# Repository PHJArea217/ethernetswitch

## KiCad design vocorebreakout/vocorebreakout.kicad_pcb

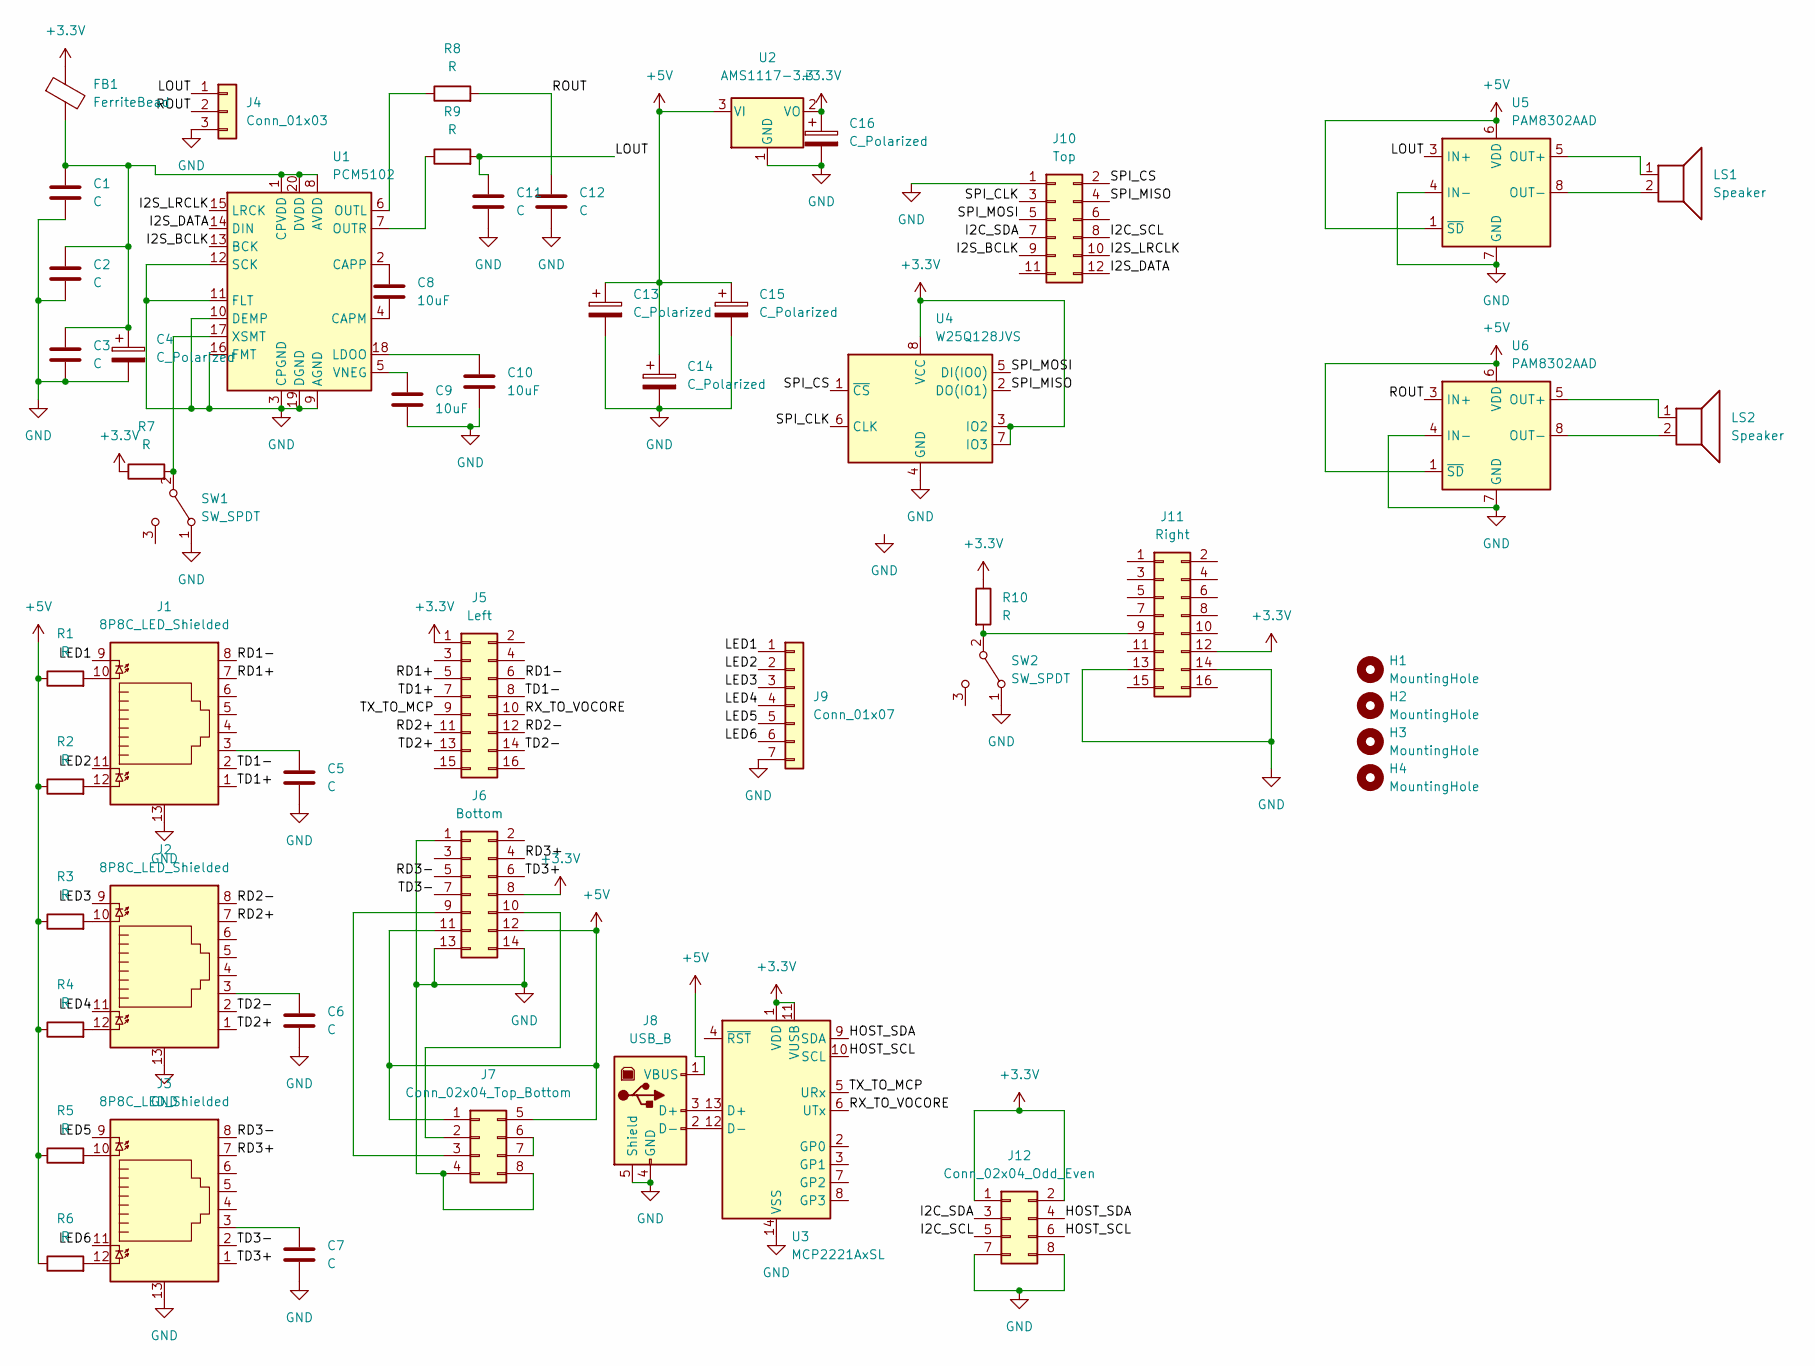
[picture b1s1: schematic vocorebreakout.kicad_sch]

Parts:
C1, C2, C3, C5, C6, C7, C11, C12: C; C_0603_1608Metric
C4, C13, C14, C15, C16: C_Polarized; CP_Radial_D8.0mm_P3.50mm
C8, C9, C10: 10uF; C_0805_2012Metric
FB1: FerriteBead; R_1206_3216Metric
H1, H2, H3, H4: MountingHole; MountingHole_3.2mm_M3
J1, J2, J3: 8P8C_LED_Shielded; RJ45_Cetus_J1B1211CCD_Horizontal
J4: Conn_01x03; PinHeader_1x03_P2.54mm_Vertical
J5: Left; PinHeader_2x08_P2.54mm_Vertical
J6: Bottom; PinHeader_2x07_P2.54mm_Vertical
J7: Conn_02x04_Top_Bottom; USB_A_Wuerth_61400826021_Horizontal_Stacked
J8: USB_B; USB_B_OST_USB-B1HSxx_Horizontal
J9: Conn_01x07; PinHeader_1x07_P2.54mm_Vertical
J10: Top; PinHeader_2x06_P2.54mm_Vertical
J11: Right; PinHeader_2x08_P2.54mm_Vertical
J12: Conn_02x04_Odd_Even; PinHeader_2x04_P2.54mm_Vertical
LS1, LS2: Speaker; PinHeader_1x02_P2.54mm_Vertical
R1, R2, R3, R4, R5, R6, R7, R8, R9, R10: R; R_0603_1608Metric
SW1, SW2: SW_SPDT; PinHeader_1x03_P2.54mm_Vertical
U1: PCM5102; TSSOP-20_4.4x6.5mm_P0.65mm
U2: AMS1117-3.3; SOT-223-3_TabPin2
U3: MCP2221AxSL; SOIC-14_3.9x8.7mm_P1.27mm
U4: W25Q128JVS; SOIC-8_5.23x5.23mm_P1.27mm
U5, U6: PAM8302AAD; SOIC-8_3.9x4.9mm_P1.27mm

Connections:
+3.3V: C16.1, FB1.1, J5.1, J6.8, J11.12, J12.1, J12.2, R7.1, R10.1, U2.2 (VO), U3.1 (VDD), U3.11 (VUSB), U4.3 (IO2), U4.7 (IO3), U4.8 (VCC)
+5V: C13.1, C14.1, C15.1, J6.11, J6.12, J7.1, J7.5, J8.1 (VBUS), R1.1, R2.1, R3.1, R4.1, R5.1, R6.1, U2.3 (VI), U5.1 (~SD), U5.6 (VDD), U6.1 (~SD), U6.6 (VDD)
/HOST_SCL: J12.6, U3.10 (SCL)
/HOST_SDA: J12.4, U3.9 (SDA)
/I2C_SCL: J10.8, J12.5
/I2C_SDA: J10.7, J12.3
/I2S_BCLK: J10.9, U1.13 (BCK)
/I2S_DATA: J10.12, U1.14 (DIN)
/I2S_LRCLK: J10.10, U1.15 (LRCK)
/LED1: J1.9, J9.1
/LED2: J1.11, J9.2
/LED3: J2.9, J9.3
/LED4: J2.11, J9.4
/LED5: J3.9, J9.5
/LED6: J3.11, J9.6
/LOUT: C11.1, J4.1, R9.2, U5.3 (IN+)
/RD1+: J1.7, J5.5
/RD1-: J1.8, J5.6
/RD2+: J2.7, J5.11
/RD2-: J2.8, J5.12
/RD3+: J3.7, J6.4
/RD3-: J3.8, J6.5
/ROUT: C12.1, J4.2, R8.2, U6.3 (IN+)
/RX_TO_VOCORE: J5.10, U3.6 (UTx)
/SPI_CLK: J10.3, U4.6 (CLK)
/SPI_CS: J10.2, U4.1 (~CS)
/SPI_MISO: J10.4, U4.2 (DO(IO1))
/SPI_MOSI: J10.5, U4.5 (DI(IO0))
/TD1+: J1.1, J5.7
/TD1-: J1.2, J5.8
/TD2+: J2.1, J5.13
/TD2-: J2.2, J5.14
/TD3+: J3.1, J6.6
/TD3-: J3.2, J6.7
/TX_TO_MCP: J5.9, U3.5 (URx)
GND: C1.2, C2.2, C3.2, C4.2, C5.2, C6.2, C7.2, C9.2, C10.2, C11.2, C12.2, C13.2, C14.2, C15.2, C16.2, J1.13, J2.13, J3.13, J4.3, J6.1, J6.13, J6.14, J7.4, J7.8, J8.4 (GND), J8.5 (Shield), J9.7, J10.1, J11.13, J11.14, J12.7, J12.8, SW1.1 (A), SW2.1 (A), U1.3 (CPGND), U1.9 (AGND), U1.10 (DEMP), U1.11 (FLT), U1.12 (SCK), U1.16 (FMT), U1.19 (DGND), U2.1 (GND), U3.14 (VSS), U4.4 (GND), U5.4 (IN-), U5.7 (GND), U6.4 (IN-), U6.7 (GND)
unnamed: C1.1, C2.1, C3.1, C4.1, FB1.2, U1.1 (CPVDD), U1.8 (AVDD), U1.20 (DVDD)
unnamed: C5.1, J1.3
unnamed: C6.1, J2.3
unnamed: C7.1, J3.3
unnamed: C8.1, U1.2 (CAPP)
unnamed: C8.2, U1.4 (CAPM)
unnamed: C9.1, U1.5 (VNEG)
unnamed: C10.1, U1.18 (LDOO)
unnamed: J1.10, R1.2
unnamed: J1.12, R2.2
unnamed: J2.10, R3.2
unnamed: J2.12, R4.2
unnamed: J3.10, R5.2
unnamed: J3.12, R6.2
unnamed: J6.9, J7.3
unnamed: J6.10, J7.2
unnamed: J7.6, J7.7
unnamed: J8.2 (D-), U3.12 (D-)
unnamed: J8.3 (D+), U3.13 (D+)
unnamed: J11.9, R10.2, SW2.2 (B)
unnamed: LS1.1, U5.5 (OUT+)
unnamed: LS1.2, U5.8 (OUT-)
unnamed: LS2.1, U6.5 (OUT+)
unnamed: LS2.2, U6.8 (OUT-)
unnamed: R7.2, SW1.2 (B), U1.17 (XSMT)
unnamed: R8.1, U1.6 (OUTL)
unnamed: R9.1, U1.7 (OUTR)

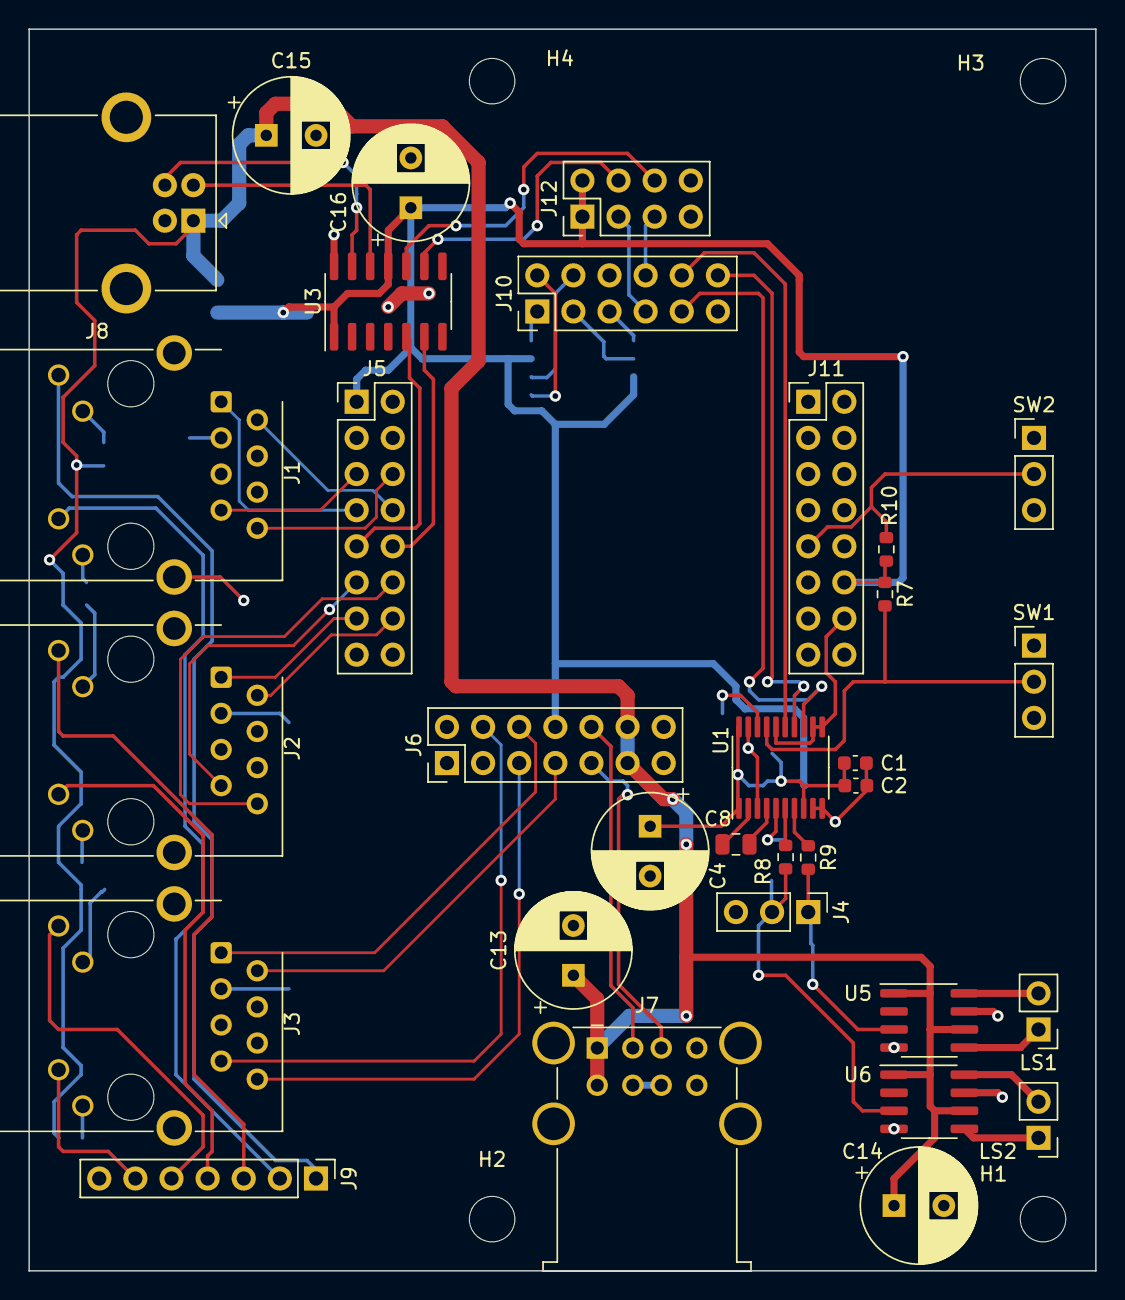
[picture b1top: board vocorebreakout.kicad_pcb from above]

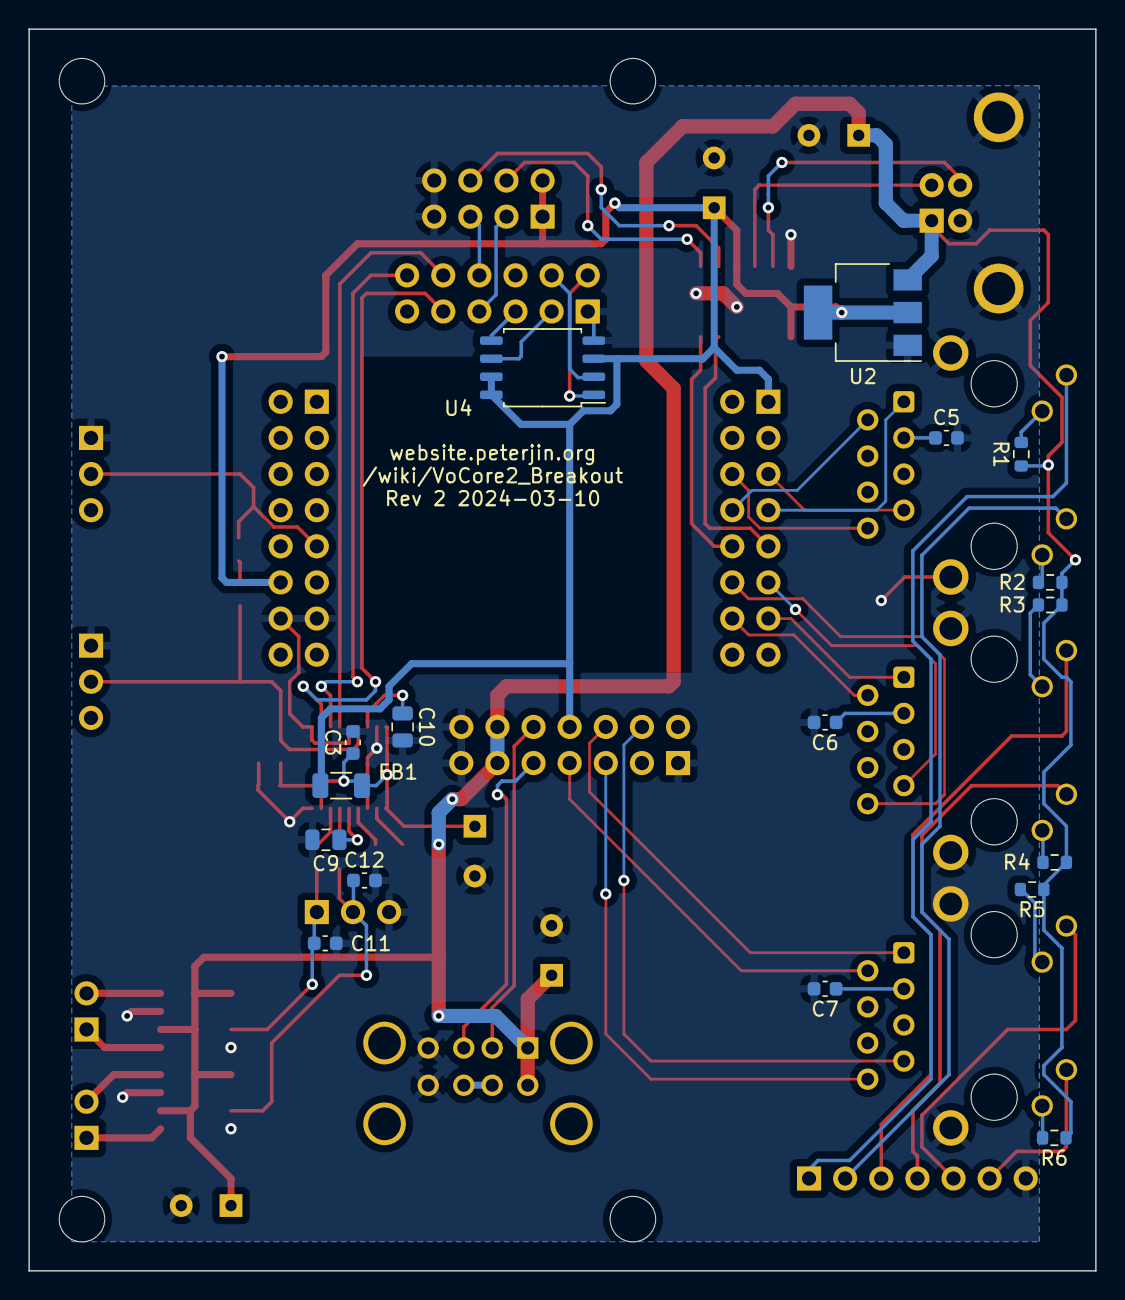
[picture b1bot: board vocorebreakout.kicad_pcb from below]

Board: 2 copper layers, 75.0 x 87.3 mm, 53 parts (17 on the bottom side), 63 nets.

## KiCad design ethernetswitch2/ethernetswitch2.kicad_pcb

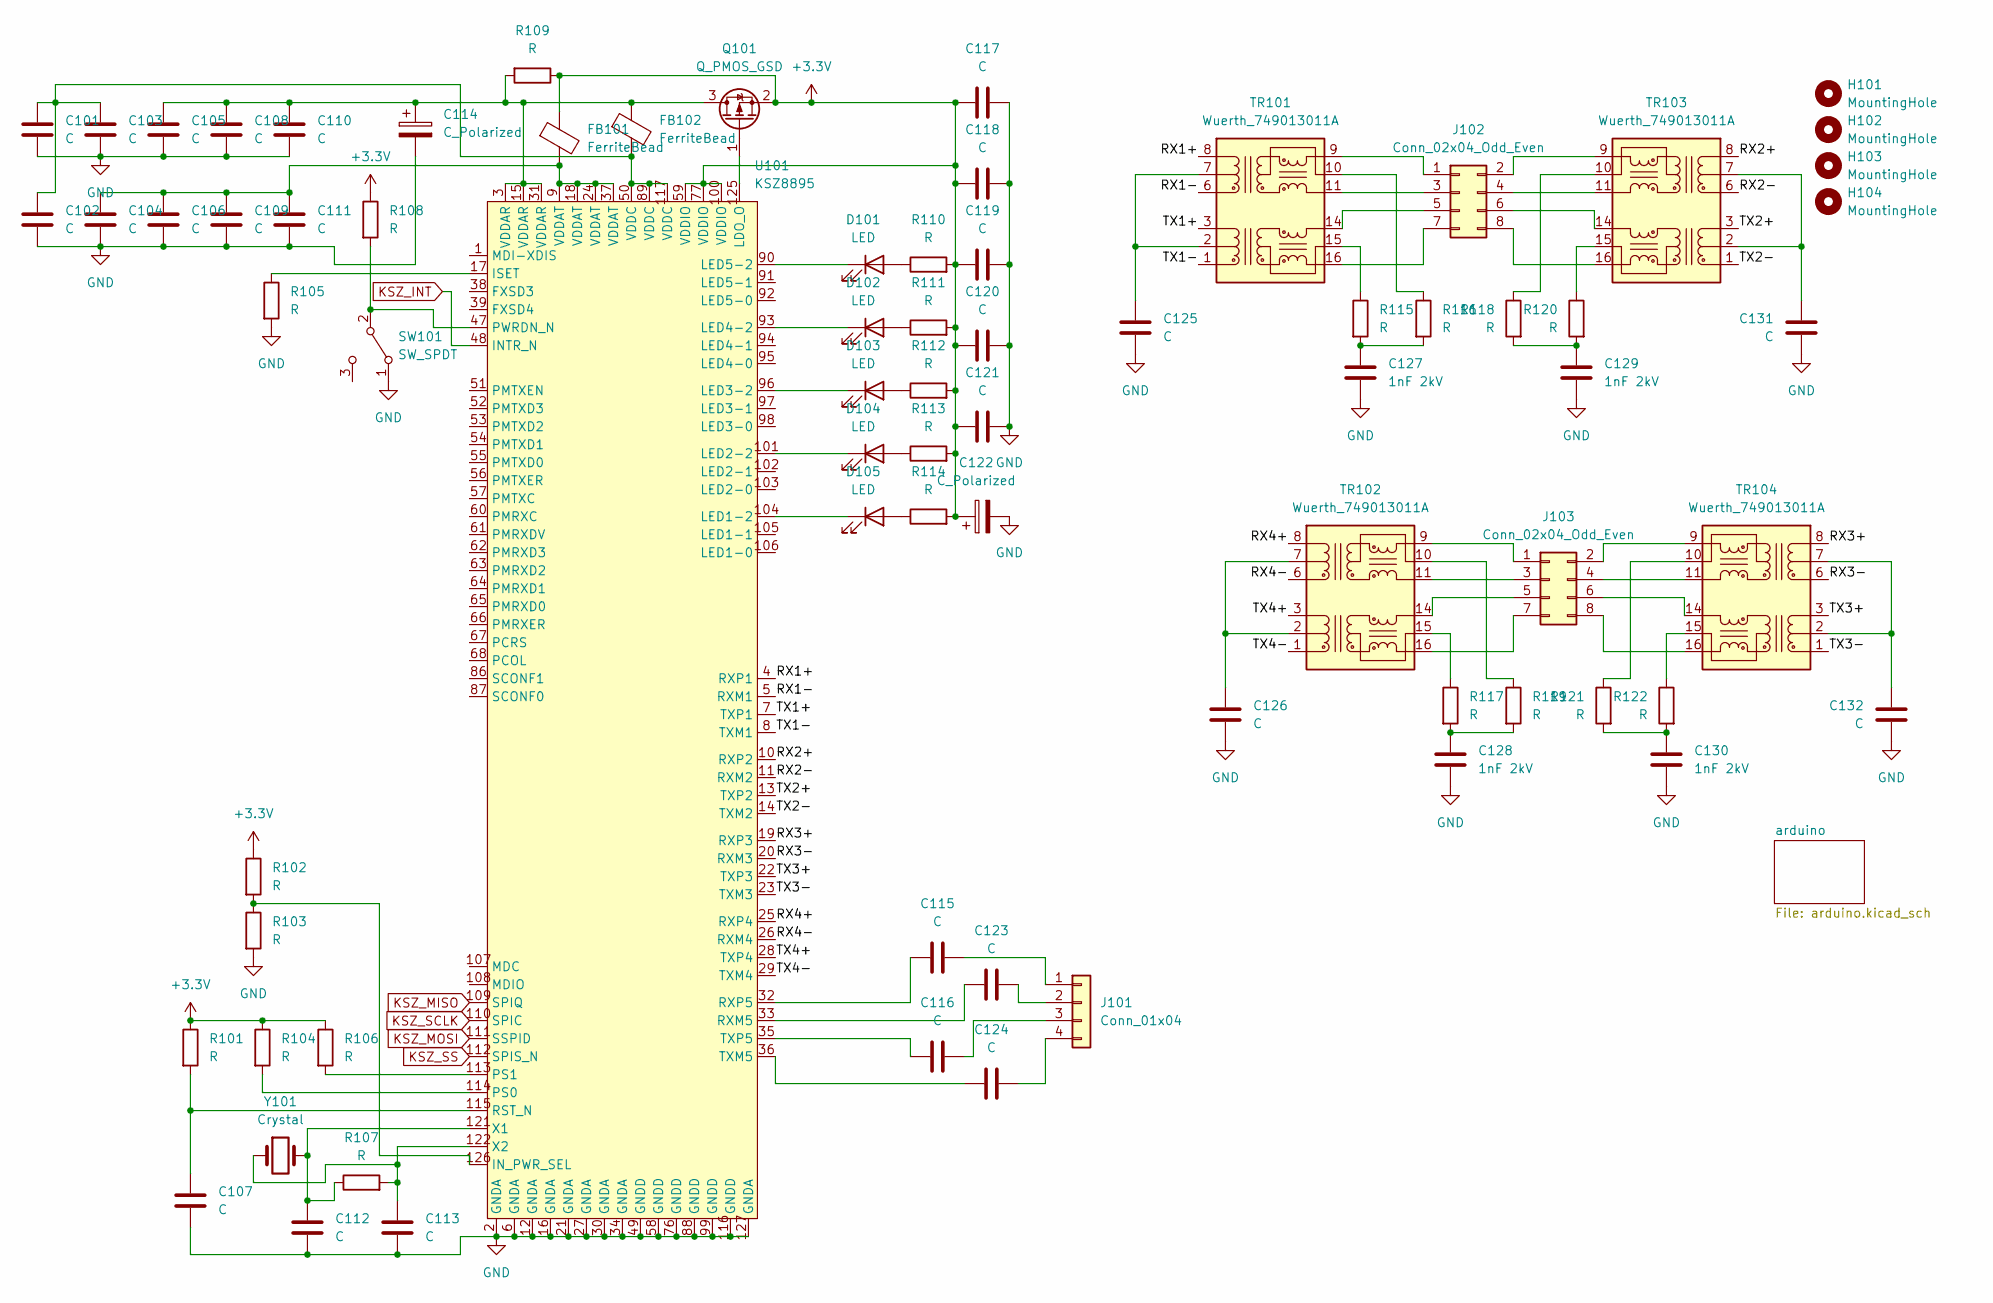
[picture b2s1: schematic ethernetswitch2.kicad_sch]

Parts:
C101, C102, C103, C104, C105, C106, C107, C108, C109, C110, C111, C112, C113, C115, C116, C117, C118, C119, C120, C121, C123, C124, C125, C126, C131, C132: C; C_0603_1608Metric
C114, C122: C_Polarized; CP_Radial_D8.0mm_P3.50mm
C127, C128, C129, C130: 1nF 2kV; C_1206_3216Metric
D101, D102, D103, D104, D105: LED; C_0603_1608Metric
FB101, FB102: FerriteBead; C_1206_3216Metric
H101, H102, H103, H104: MountingHole; MountingHole_3.2mm_M3
J101: Conn_01x04; PinHeader_1x04_P2.54mm_Vertical
J102, J103: Conn_02x04_Odd_Even; PinHeader_2x04_P2.54mm_Vertical
Q101: Q_PMOS_GSD; SOT-23-3
R101, R102, R103, R104, R105, R106, R107, R108, R109, R110, R111, R112, R113, R114, R115, R116, R117, R118, R119, R120, R121, R122: R; R_0603_1608Metric
SW101: SW_SPDT; PinHeader_1x03_P2.54mm_Vertical
TR101, TR102, TR103, TR104: Wuerth_749013011A; Transformer_Ethernet_Wuerth_749013011A
U101: KSZ8895; LQFP-128_14x20mm_P0.5mm
Y101: Crystal; Crystal_HC49-U_Vertical

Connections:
+3.3V: C117.1, C118.1, C119.1, C120.1, C121.1, C122.1, FB101.1, Q101.2 (S), R101.1, R102.1, R104.1, R106.1, R108.1, R109.1, R110.2, R111.2, R112.2, R113.2, R114.2, U101.59 (VDDIO), U101.77 (VDDIO), U101.100 (VDDIO); also elsewhere on the board
/RX1+: TR101.8 (RD-), U101.4 (RXP1)
/RX1-: TR101.6 (RD+), U101.5 (RXM1)
/RX2+: TR103.8 (RD-), U101.10 (RXP2)
/RX2-: TR103.6 (RD+), U101.11 (RXM2)
/RX3+: TR104.8 (RD-), U101.19 (RXP3)
/RX3-: TR104.6 (RD+), U101.20 (RXM3)
/RX4+: TR102.8 (RD-), U101.25 (RXP4)
/RX4-: TR102.6 (RD+), U101.26 (RXM4)
/TX1+: TR101.3 (TD-), U101.7 (TXP1)
/TX1-: TR101.1 (TD+), U101.8 (TXM1)
/TX2+: TR103.3 (TD-), U101.13 (TXP2)
/TX2-: TR103.1 (TD+), U101.14 (TXM2)
/TX3+: TR104.3 (TD-), U101.22 (TXP3)
/TX3-: TR104.1 (TD+), U101.23 (TXM3)
/TX4+: TR102.3 (TD-), U101.28 (TXP4)
/TX4-: TR102.1 (TD+), U101.29 (TXM4)
GND: C101.2, C102.2, C103.2, C104.2, C105.2, C106.2, C107.2, C108.2, C109.2, C110.2, C111.2, C112.2, C113.2, C114.2, C117.2, C118.2, C119.2, C120.2, C121.2, C122.2, C125.2, C126.2, C127.2, C128.2, C129.2, C130.2, C131.2, C132.2, R103.2, R105.2, SW101.1 (A), U101.2 (GNDA), U101.6 (GNDA), U101.12 (GNDA), U101.16 (GNDA), U101.21 (GNDA), U101.27 (GNDA), U101.30 (GNDA), U101.34 (GNDA), U101.49 (GNDD), U101.58 (GNDD), U101.76 (GNDD), U101.88 (GNDD), U101.99 (GNDD), U101.116 (GNDD), U101.127 (GNDA); also elsewhere on the board
KSZ_INT: U101.48 (INTR_N); also elsewhere on the board
KSZ_MISO: U101.109 (SPIQ); also elsewhere on the board
KSZ_MOSI: U101.111 (SSPID); also elsewhere on the board
KSZ_SCLK: U101.110 (SPIC); also elsewhere on the board
KSZ_SS: U101.112 (SPIS_N); also elsewhere on the board
unnamed: C101.1, C102.1, C103.1, FB102.2, U101.50 (VDDC), U101.89 (VDDC), U101.117 (VDDC)
unnamed: C104.1, C106.1, C109.1, C111.1, FB101.2, U101.9 (VDDAT), U101.18 (VDDAT), U101.24 (VDDAT), U101.37 (VDDAT)
unnamed: C105.1, C108.1, C110.1, C114.1, FB102.1, Q101.3 (D), R109.2, U101.3 (VDDAR), U101.15 (VDDAR), U101.31 (VDDAR)
unnamed: C107.1, R101.2, U101.115 (RST_N)
unnamed: C112.1, R107.1, U101.121 (X1), Y101.2
unnamed: C113.1, R107.2, U101.122 (X2), Y101.1
unnamed: C115.1, U101.32 (RXP5)
unnamed: C115.2, J101.1
unnamed: C116.1, U101.35 (TXP5)
unnamed: C116.2, J101.3
unnamed: C123.1, U101.33 (RXM5)
unnamed: C123.2, J101.2
unnamed: C124.1, U101.36 (TXM5)
unnamed: C124.2, J101.4
unnamed: C125.1, TR101.2 (C_TD), TR101.7 (C_RD)
unnamed: C126.1, TR102.2 (C_TD), TR102.7 (C_RD)
unnamed: C127.1, R115.2, R116.2
unnamed: C128.1, R117.2, R119.2
unnamed: C129.1, R118.2, R120.2
unnamed: C130.1, R121.2, R122.2
unnamed: C131.1, TR103.2 (C_TD), TR103.7 (C_RD)
unnamed: C132.1, TR104.2 (C_TD), TR104.7 (C_RD)
unnamed: D101.1 (K), U101.90 (LED5-2)
unnamed: D101.2 (A), R110.1
unnamed: D102.1 (K), U101.93 (LED4-2)
unnamed: D102.2 (A), R111.1
unnamed: D103.1 (K), U101.96 (LED3-2)
unnamed: D103.2 (A), R112.1
unnamed: D104.1 (K), U101.101 (LED2-2)
unnamed: D104.2 (A), R113.1
unnamed: D105.1 (K), U101.104 (LED1-2)
unnamed: D105.2 (A), R114.1
unnamed: J102.1, TR101.9 (RX-)
unnamed: J102.2, TR103.9 (RX-)
unnamed: J102.3, TR101.11 (RX+)
unnamed: J102.4, TR103.11 (RX+)
unnamed: J102.5, TR101.14 (TX-)
unnamed: J102.6, TR103.14 (TX-)
unnamed: J102.7, TR101.16 (TX+)
unnamed: J102.8, TR103.16 (TX+)
unnamed: J103.1, TR102.9 (RX-)
unnamed: J103.2, TR104.9 (RX-)
unnamed: J103.3, TR102.11 (RX+)
unnamed: J103.4, TR104.11 (RX+)
unnamed: J103.5, TR102.14 (TX-)
unnamed: J103.6, TR104.14 (TX-)
unnamed: J103.7, TR102.16 (TX+)
unnamed: J103.8, TR104.16 (TX+)
unnamed: Q101.1 (G), U101.125 (LDO_O)
unnamed: R102.2, R103.1, U101.126 (IN_PWR_SEL)
unnamed: R104.2, U101.114 (PS0)
unnamed: R105.1, U101.17 (ISET)
unnamed: R106.2, U101.113 (PS1)
unnamed: R108.2, SW101.2 (B), U101.47 (PWRDN_N)
unnamed: R115.1, TR101.15 (C_TX)
unnamed: R116.1, TR101.10 (C_RX)
unnamed: R117.1, TR102.15 (C_TX)
unnamed: R118.1, TR103.10 (C_RX)
unnamed: R119.1, TR102.10 (C_RX)
unnamed: R120.1, TR103.15 (C_TX)
unnamed: R121.1, TR104.10 (C_RX)
unnamed: R122.1, TR104.15 (C_TX)

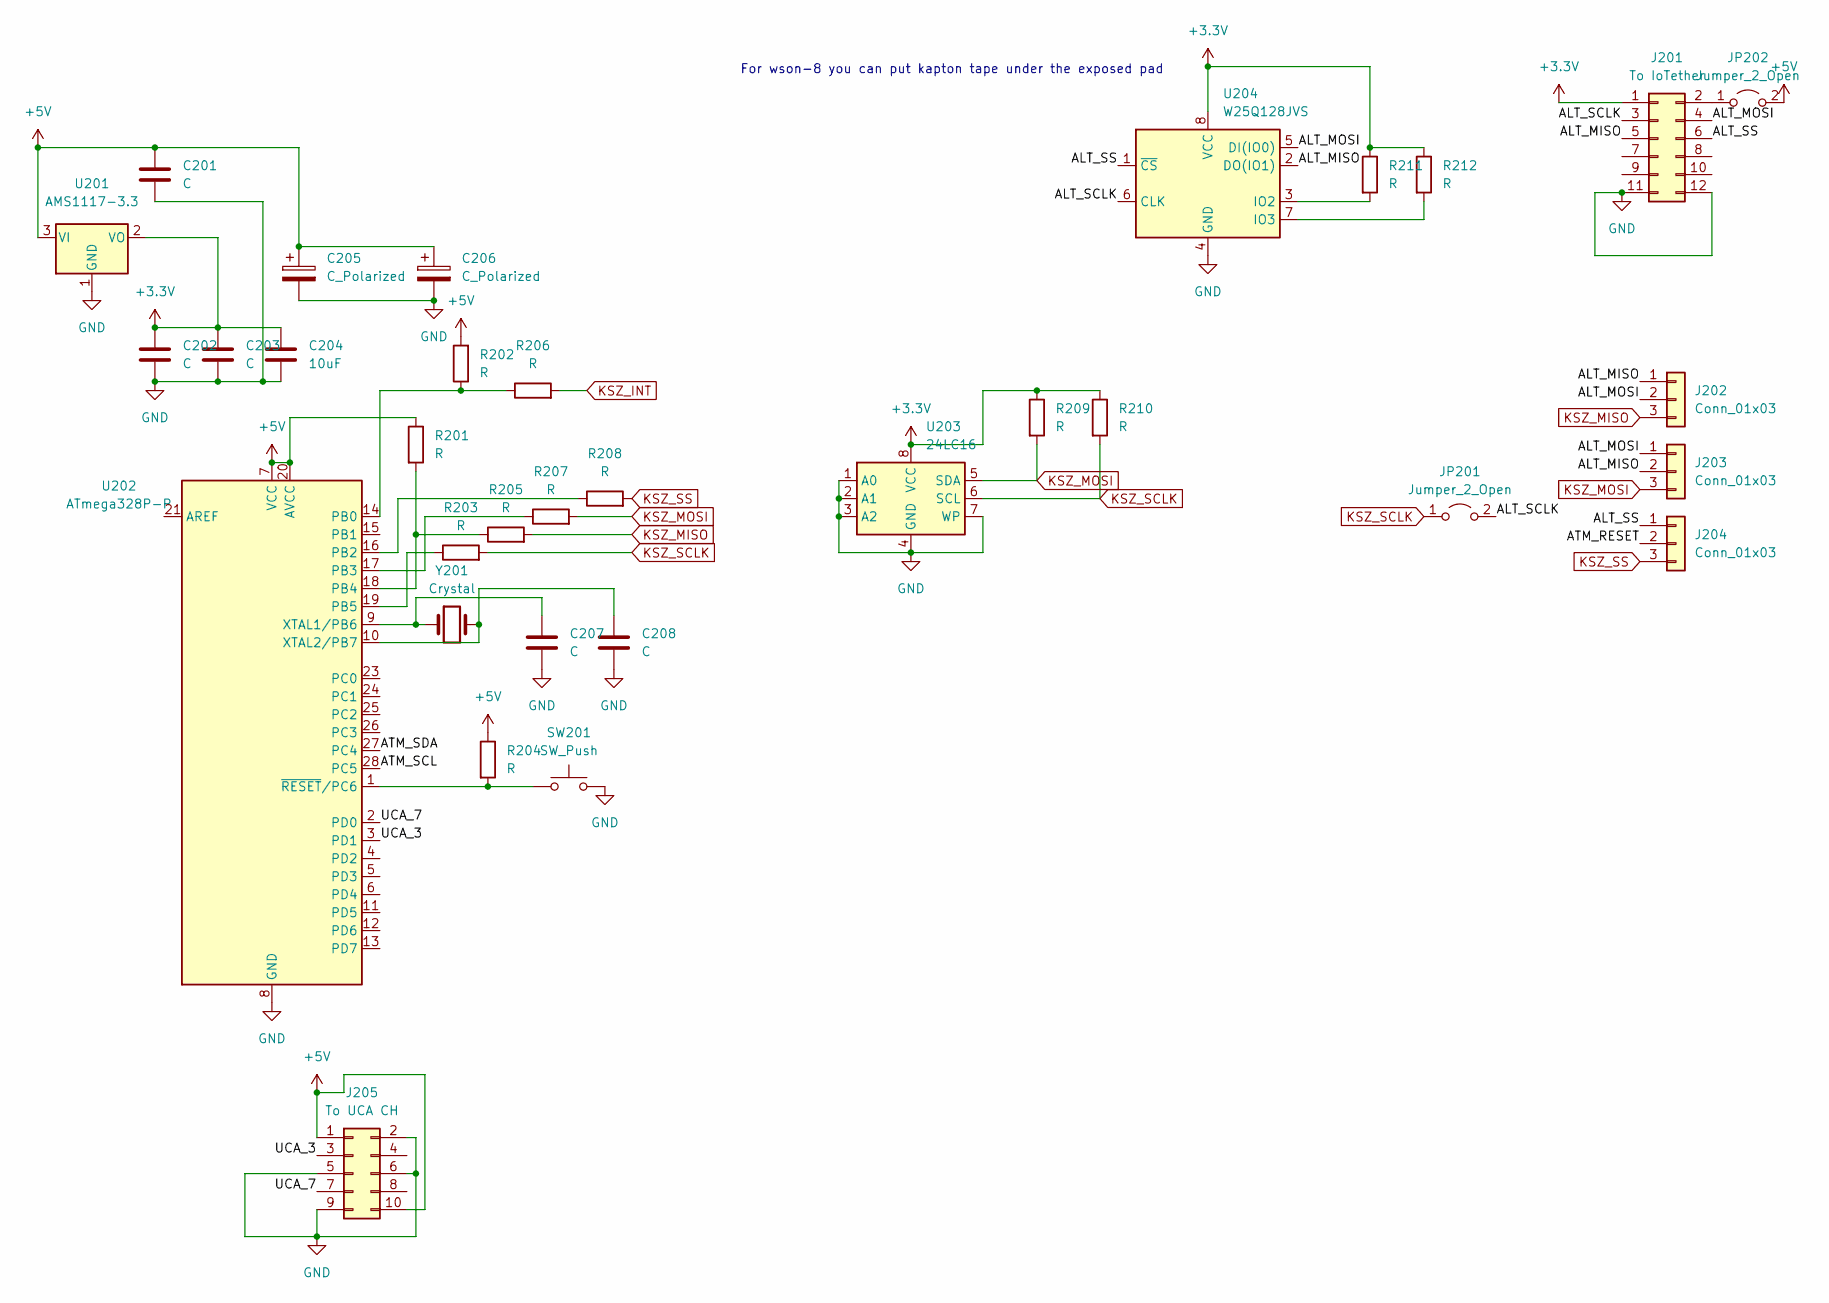
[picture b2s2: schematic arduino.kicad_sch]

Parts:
C201, C202, C203, C207, C208: C; C_0603_1608Metric
C204: 10uF; C_0805_2012Metric
C205, C206: C_Polarized; CP_Radial_D8.0mm_P3.50mm
J201: To IoTether; PinHeader_2x06_P2.54mm_Vertical
J202, J203, J204: Conn_01x03; SOT-23-3
J205: To UCA CH; PinHeader_2x05_P2.54mm_Horizontal
JP201, JP202: Jumper_2_Open; R_0603_1608Metric
R201, R202, R203, R204, R205, R206, R207, R208, R209, R210, R211, R212: R; R_0603_1608Metric
SW201: SW_Push; SW_PUSH_6mm
U201: AMS1117-3.3; SOT-223-3_TabPin2
U202: ATmega328P-P; DIP-28_W7.62mm_Socket
U203: 24LC16; DIP-8_W7.62mm_Socket
U204: W25Q128JVS; SOIC-8_5.23x5.23mm_P1.27mm
Y201: Crystal; Crystal_HC49-U_Vertical

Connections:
+3.3V: C202.1, C203.1, C204.1, J201.1, R209.1, R210.1, R211.1, R212.1, U201.2 (VO), U203.8 (VCC), U204.8 (VCC); also elsewhere on the board
+5V: C201.1, C205.1, C206.1, J205.1, J205.10, JP202.2 (B), R201.1, R202.2, R204.1, U201.3 (VI), U202.7 (VCC), U202.20 (AVCC)
/arduino/ALT_MISO: J201.5, J202.1, J203.2, U204.2 (DO(IO1))
/arduino/ALT_MOSI: J201.4, J202.2, J203.1, U204.5 (DI(IO0))
/arduino/ALT_SCLK: J201.3, JP201.2 (B), U204.6 (CLK)
/arduino/ALT_SS: J201.6, J204.1, U204.1 (~CS)
/arduino/ATM_RESET: J204.2
/arduino/ATM_SCL: U202.28 (PC5)
/arduino/ATM_SDA: U202.27 (PC4)
/arduino/UCA_3: J205.3, U202.3 (PD1)
/arduino/UCA_7: J205.7, U202.2 (PD0)
GND: C201.2, C202.2, C203.2, C204.2, C205.2, C206.2, C207.2, C208.2, J201.11, J201.12, J205.2, J205.5, J205.6, J205.9, SW201.2, U201.1 (GND), U202.8 (GND), U202.22 (GND), U203.1 (A0), U203.2 (A1), U203.3 (A2), U203.4 (GND), U203.7 (WP), U204.4 (GND); also elsewhere on the board
KSZ_INT: R206.2; also elsewhere on the board
KSZ_MISO: J202.3, R205.2; also elsewhere on the board
KSZ_MOSI: J203.3, R207.2, R209.2, U203.5 (SDA); also elsewhere on the board
KSZ_SCLK: JP201.1 (A), R203.2, R210.2, U203.6 (SCL); also elsewhere on the board
KSZ_SS: J204.3, R208.2; also elsewhere on the board
unnamed: C207.1, U202.9 (XTAL1/PB6), Y201.1
unnamed: C208.1, U202.10 (XTAL2/PB7), Y201.2
unnamed: J201.2, JP202.1 (A)
unnamed: R201.2, R205.1, U202.18 (PB4)
unnamed: R202.1, R206.1, U202.14 (PB0)
unnamed: R203.1, U202.19 (PB5)
unnamed: R204.2, SW201.1, U202.1 (~RESET/PC6)
unnamed: R207.1, U202.17 (PB3)
unnamed: R208.1, U202.16 (PB2)
unnamed: R211.2, U204.3 (IO2)
unnamed: R212.2, U204.7 (IO3)

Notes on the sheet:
For wson-8 you can put kapton tape under the exposed pad

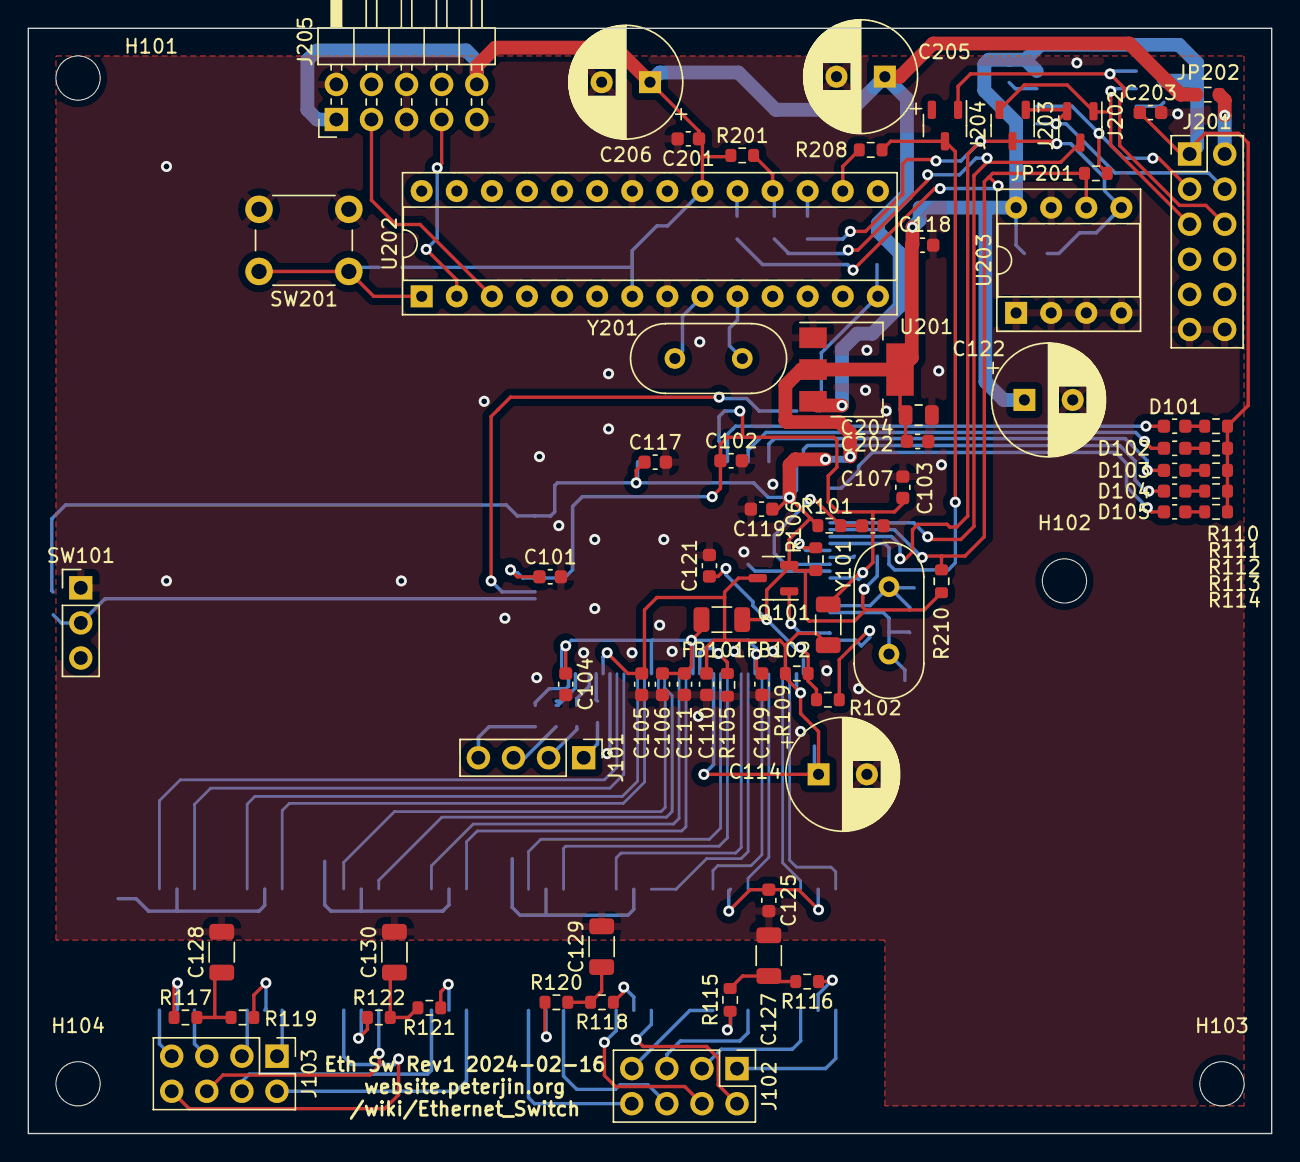
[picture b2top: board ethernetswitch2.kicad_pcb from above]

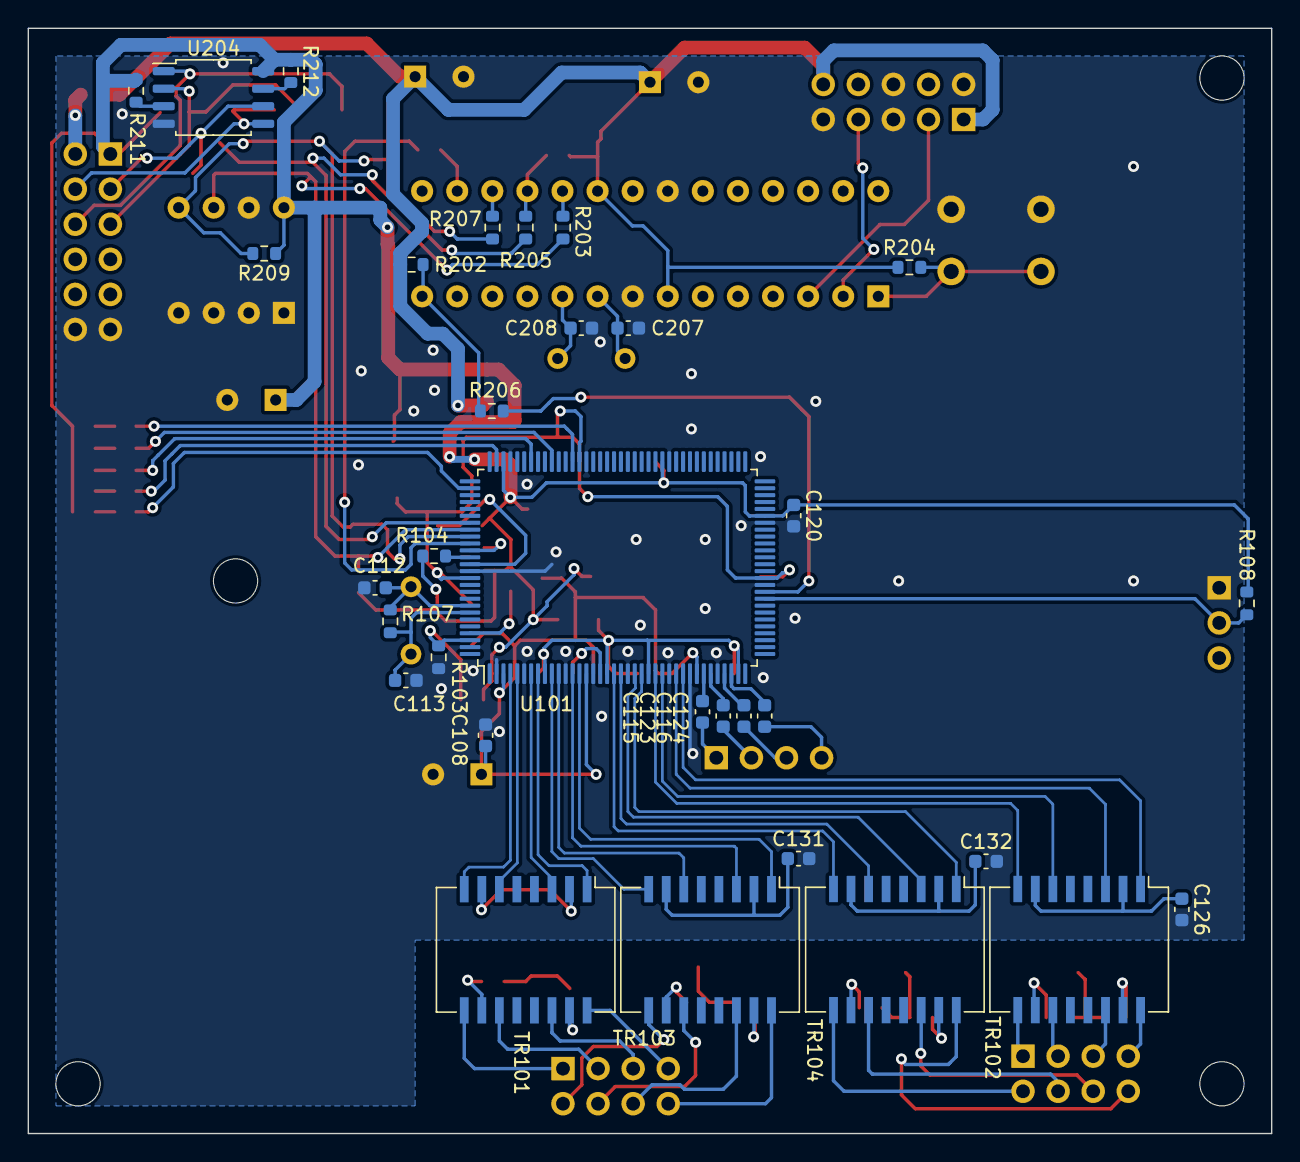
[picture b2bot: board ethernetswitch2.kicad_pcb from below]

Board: 2 copper layers, 90.0 x 80.0 mm, 109 parts (32 on the bottom side), 103 nets.

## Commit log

2024-02-18 Add KSZ8895 symbol
2024-03-10 vocorebreakout: Move SPI flash to bottom and ethernet port to #2
